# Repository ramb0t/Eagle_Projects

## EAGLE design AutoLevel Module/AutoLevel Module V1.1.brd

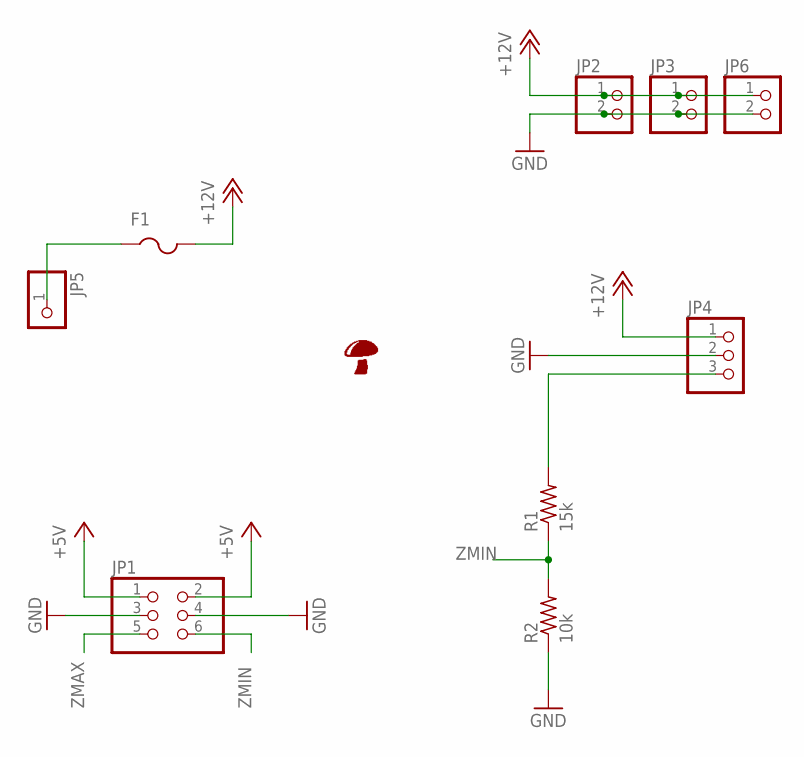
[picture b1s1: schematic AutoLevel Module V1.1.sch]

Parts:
F1: PTCFUSE-1812; 1812
JP1: PINHD-2X3; 2X03
JP2, JP3, JP6: PINHD-1X2; 1X02
JP4: PINHD-1X3; 1X03
JP5: PINHD-1X1; 1X01
R1: 15k; R0805
R2: 10k; R0805
U$1: SHROOM5MM; SHROOM

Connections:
+5V: JP1.1, JP1.2
+12V: F1.2, JP2.1, JP3.1, JP4.1, JP6.1
GND: JP1.3, JP1.4, JP2.2, JP3.2, JP4.2, JP6.2, R2.1
unnamed: F1.1, JP5.1
unnamed: JP4.3, R1.2
ZMAX: JP1.5
ZMIN: JP1.6, R1.1, R2.2

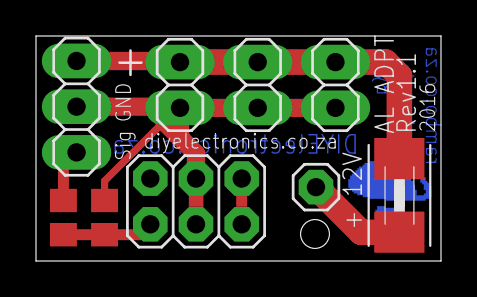
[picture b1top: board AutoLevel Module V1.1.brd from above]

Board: 2 copper layers, 22.5 x 12.5 mm, 10 parts (1 on the bottom side), 6 nets.

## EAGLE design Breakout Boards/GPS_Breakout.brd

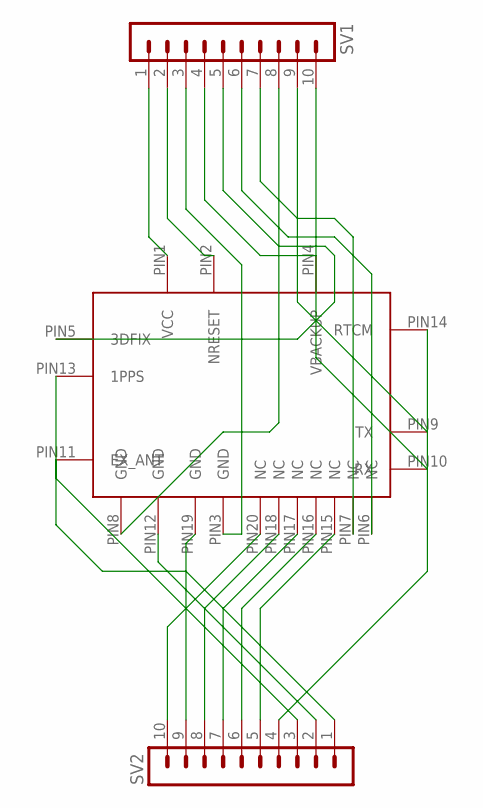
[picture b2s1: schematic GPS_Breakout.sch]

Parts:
SV1, SV2: MA10-1
U$1: GPS_FGPMMOPA6H; FGPMMOPA6H_FOOTPRINT

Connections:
unnamed: SV1.1, U$1.PIN1 (VCC)
unnamed: SV1.2, U$1.PIN2 (NRESET)
unnamed: SV1.3, U$1.PIN3 (GND)
unnamed: SV1.4, U$1.PIN4 (VBACKUP)
unnamed: SV1.5, U$1.PIN5 (3DFIX)
unnamed: SV1.6, U$1.PIN6 (NC)
unnamed: SV1.7, U$1.PIN7 (NC)
unnamed: SV1.8, U$1.PIN8 (GND)
unnamed: SV1.9, U$1.PIN9 (TX)
unnamed: SV1.10, U$1.PIN10 (RX)
unnamed: SV2.1, U$1.PIN11 (EX_ANT)
unnamed: SV2.2, U$1.PIN12 (GND)
unnamed: SV2.3, U$1.PIN13 (1PPS)
unnamed: SV2.4, U$1.PIN14 (RTCM)
unnamed: SV2.5, U$1.PIN15 (NC)
unnamed: SV2.6, U$1.PIN16 (NC)
unnamed: SV2.7, U$1.PIN17 (NC)
unnamed: SV2.8, U$1.PIN18 (NC)
unnamed: SV2.9, U$1.PIN19 (GND)
unnamed: SV2.10, U$1.PIN20 (NC)

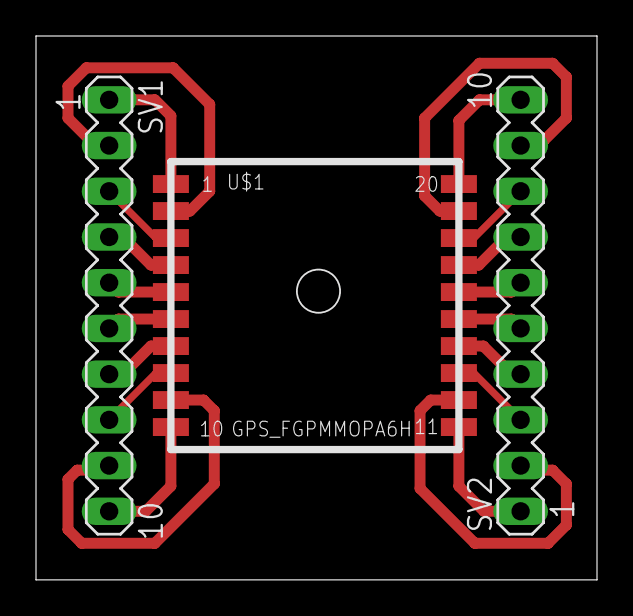
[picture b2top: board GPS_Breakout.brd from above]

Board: 2 copper layers, 31.2 x 30.2 mm, 3 parts (0 on the bottom side), 20 nets.
